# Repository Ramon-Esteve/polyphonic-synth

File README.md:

# DIY Polyphonic Analog Synthesizer

A university project building a polyphonic analog synthesizer from scratch using [mki x es.EDU](https://www.ericasynths.lv/shop/diy-kits-1/mki-x-esedu-diy-system/) module designs and an STM32 Nucleo board as a MIDI-to-CV controller.

The goal is to go from a single voice on a breadboard to a playable multi-voice analog synth controlled via MIDI — while documenting every step of the process.

## What This Project Is

This is an educational build that combines:
- **Analog circuit design** — VCO, VCF, VCA and envelope circuits based on the publicly available Erica Synths / Moritz Klein educational module designs
- **Embedded firmware** — STM32 Nucleo running custom MIDI-to-CV firmware (MIDI parsing, DAC output, voice allocation)
- **System integration** — bridging the digital (MIDI) and analog (CV/gate) worlds to create a playable instrument

All analog circuits are prototyped on breadboard. The Nucleo board handles MIDI input and outputs control voltages (1V/oct pitch CV, gate, and additional CV for filter/PWM) through its DAC and an op-amp scaling stage.

## Current Status

> **Phase 1 — VCO + MIDI pitch control** *(in progress)*

- [x] VCO built and working on breadboard
- [x] VCO on dedicated PCB (`220526_VCO_V2`) — validated and tested under real circuit conditions
- [ ] Nucleo DAC output verified
- [ ] Op-amp CV scaling circuit (0–3.3V → 0–5V)
- [ ] MIDI input (USB or UART @ 31250 baud)
- [ ] MIDI note-to-CV conversion with 1V/oct tracking
- [ ] Gate output
- [ ] Calibration and tuning

## Build Phases

| Phase | Module | Description | Status |
|-------|--------|-------------|--------|
| 1 | VCO + MIDI-to-CV | Pitch control of a single oscillator via MIDI keyboard | In progress |
| 2 | VCA + Envelope | Amplitude control with gate/envelope from Nucleo | Planned |
| 3 | VCF | Voltage-controlled filter with CV control of cutoff | Planned |
| 4 | Polyphony | Duplicate voice chains, multi-channel DAC, voice allocation | Planned |

## Hardware

- **Microcontroller:** STM32 Nucleo board (<!-- replace with your specific model, e.g. Nucleo-F446RE -->)
- **Analog modules:** Based on mki x es.EDU circuit designs (VCO, VCA, VCF, Envelope)
- **Prototyping:** Breadboard (switched from stripboard after killing two ICs soldering — lesson learned)
- **DAC output stage:** Op-amp scaling circuit to convert Nucleo's 0–3.3V DAC to 0–5V+ for 1V/oct

## VCO V2 — Bring-Up & Verification (June 2026)

The first custom VCO PCB revision (`220526_VCO_V2`, JLCPCB) has passed full bring-up and verification.

**Verified:**
- Power integrity: rails at ±11.8/−11.9 V, both wire-bridged traces (−12V rail, R7 network) confirmed functional (0.4 Ω continuity, voltage-verified under load)
- Full signal chain: saw core → buffer → AC coupling → ×3.13 gain stage → SAW out (~10 Vpp), comparator → divider → PULSE out (8.88 Vpp)
- PWM: full duty sweep functional, clean latch behaviour only at threshold extremes (by design)
- Frequency range: **~5 Hz to ~49.8 kHz** (full audio range + LFO territory)
- **V/oct tracking: ~10 cents over 2 octaves** after trimming ADJ_TUNE1, verified via Voxengo SPAN — better than the breadboard baseline (~14 ct/oct). Residual error will be handled by the planned STM32 autotune routine.

**Known issues → fixed in V0.2:**
- D4 LED footprint connects to the CV summing node instead of the buffered SAW output (not populated on V2)
- Two manufacturing trace defects bridged with wire (new revision removes bridges)
- Expo converter (BC548/BC558 discrete pair) to be replaced with monolithic matched pair (BC847BS) + tempco resistor

Full measurement protocol: [`docs/bringup_vco_v2/bringup_checklist_VCO_V2.md`](docs/bringup_vco_v2/bringup_checklist_VCO_V2.md)
Test equipment: Tektronix 2225, TOOLTOP ET828 Pro, PeakTech 6225A, RME Fireface + Voxengo SPAN

| VCO V2 PCB | Square wave output on scope |
|---|---|
|  |  |
## Repository Structure

```
├── docs/                   # Build documentation for each module
├── firmware/               # STM32CubeIDE project — MIDI-to-CV firmware
├── schematics/             # Circuit diagrams and breadboard layouts
├── measurements/           # Tuning data, oscilloscope captures, test results
├── media/                  # Build photos, video material, audio samples
└── references/             # Datasheets, links, related projects
```

## Documentation

Each build phase is documented with:
- Circuit description and design rationale
- Breadboard layout and build notes
- Test procedures and measurements
- Problems encountered and how they were solved

Video documentation accompanies the written docs — see the [media/](media/) folder or the <!-- add link to your YouTube/channel here --> video series.

## Key References

- [mki x es.EDU module manuals](https://www.ericasynths.lv/shop/diy-kits-1/mki-x-esedu-diy-system/) — free PDFs covering circuit design from scratch
- [Moritz Klein's YouTube channel](https://www.youtube.com/@MoritzKlein0) — companion videos to the EDU modules
- [ModSynth MIDI2CV](https://warrantyvoids.github.io/ModSynth/modules/midi2cv/) — STM32 Nucleo-based MIDI-to-CV reference project
- [STM32 DAC getting started](https://wiki.st.com/stm32mcu/wiki/Getting_started_with_DAC) — official ST tutorial

## License

This project is licensed under the MIT License — see [LICENSE](LICENSE) for details.

Note: The analog circuit designs are based on the mki x es.EDU educational series by Erica Synths and Moritz Klein. Their manuals are freely available but the original designs remain their work. This repository contains my own implementation, firmware, documentation, and modifications.

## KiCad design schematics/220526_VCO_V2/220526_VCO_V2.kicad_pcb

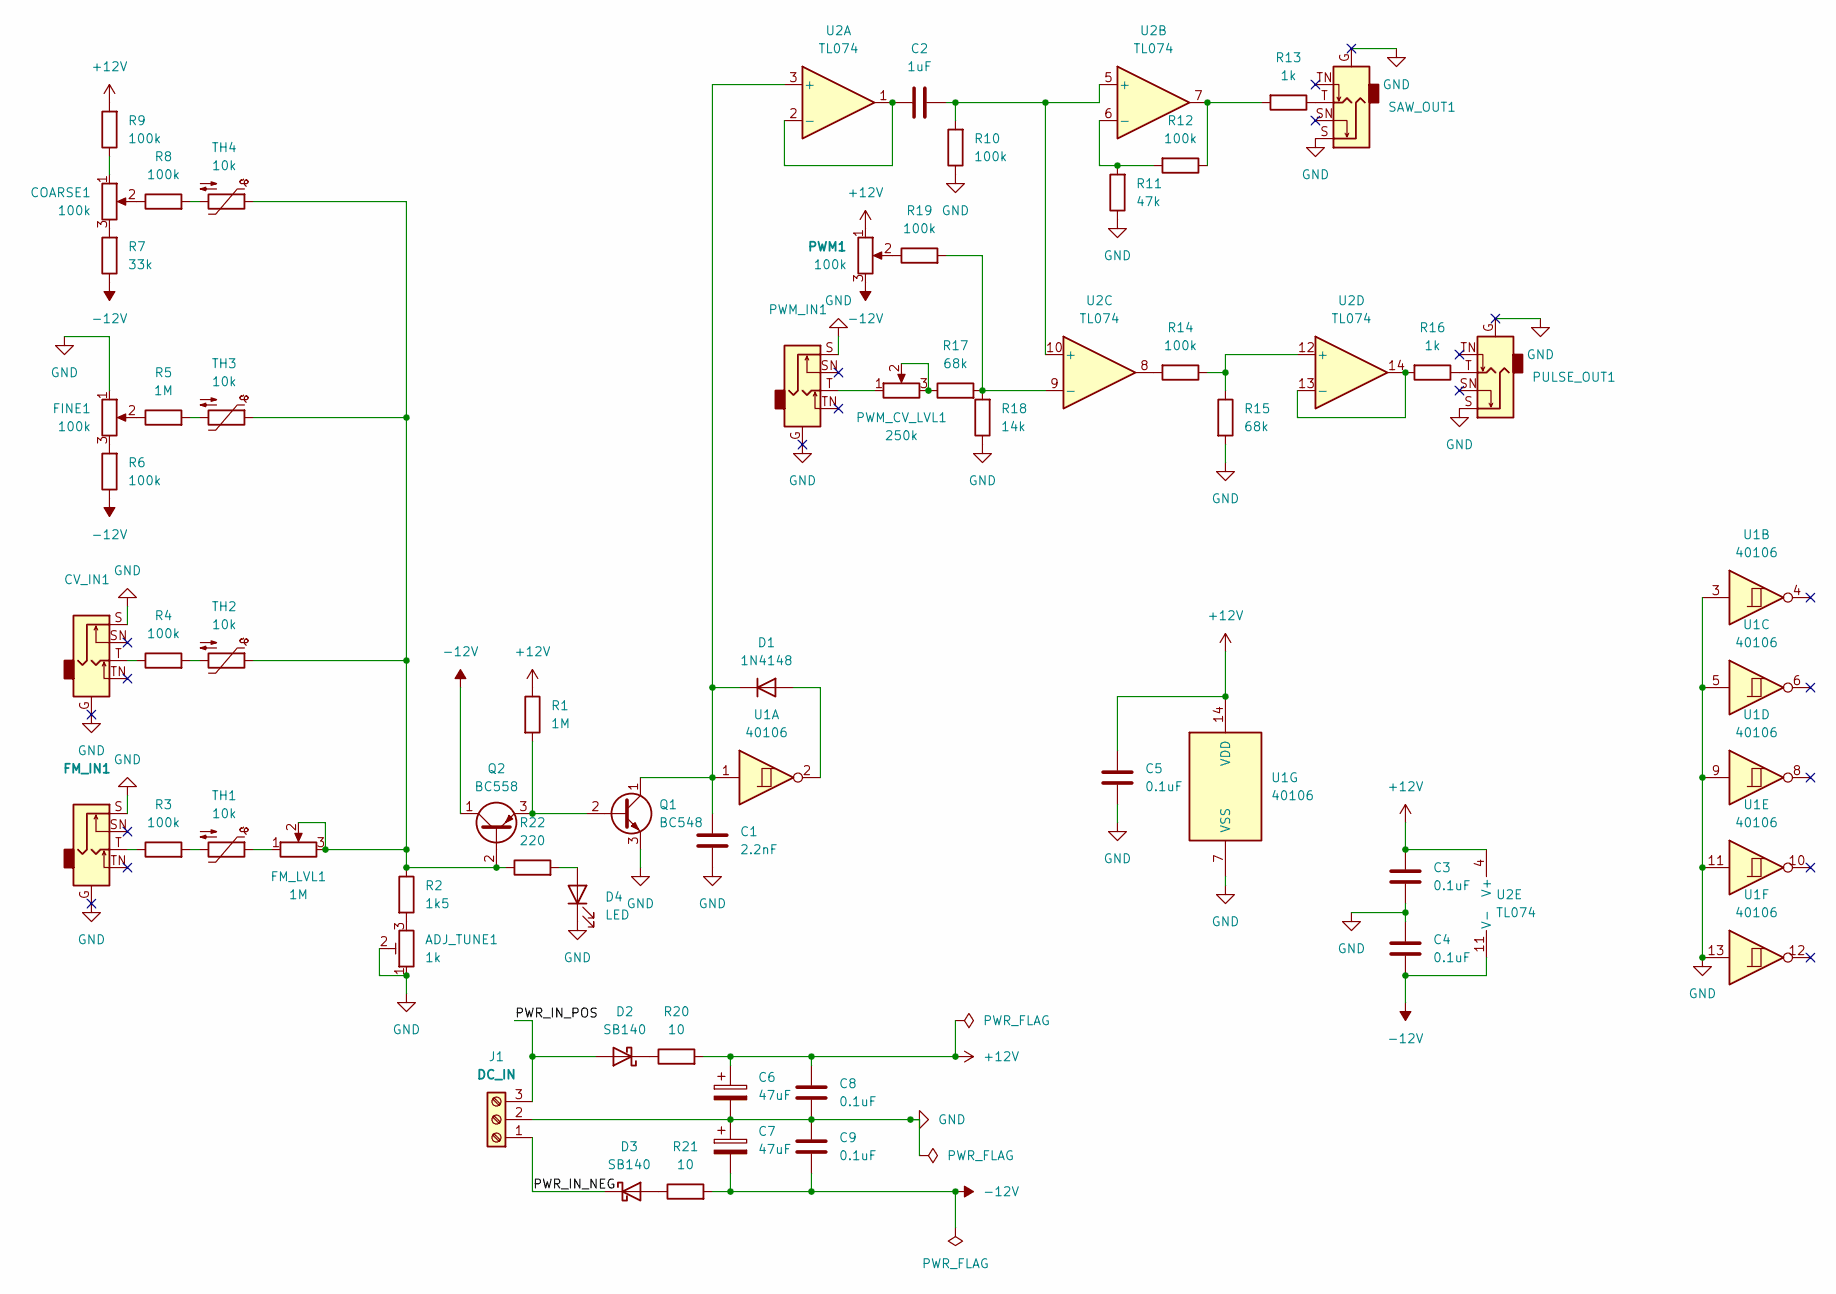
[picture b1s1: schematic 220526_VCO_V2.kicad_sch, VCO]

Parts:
ADJ_TUNE1: 1k; Potentiometer_Bourns_3266W_Vertical
C1: 2.2nF; C_Rect_L13.0mm_W4.0mm_P10.00mm_FKS3_FKP3_MKS4
C2: 1uF; C_Rect_L7.2mm_W5.0mm_P5.00mm
C3, C4, C5, C8, C9: 0.1uF; C_Disc_D5.1mm_W3.2mm_P5.00mm
C6, C7: 47uF; C_Radial_D5.0mm_H11.0mm_P2.00mm
COARSE1: 100k; Potentiometer_Omeg_PC16BU_Vertical
CV_IN1: AudioJack2_Ground_Switch; Jack_3.5mm_Cliff_FCR1281_Horizontal
D1: 1N4148; D_DO-35_SOD27_P7.62mm_Horizontal
D2, D3: SB140; D_DO-41_SOD81_P10.16mm_Horizontal
D4: LED; LED_D5.0mm
FINE1: 100k; Potentiometer_Omeg_PC16BU_Vertical
FM_IN1: AudioJack2_Ground_Switch; Jack_3.5mm_Cliff_FCR1281_Horizontal
FM_LVL1: 1M; Potentiometer_Omeg_PC16BU_Vertical
J1: DC_IN; TerminalBlock_RND_205-00288_1x03_P5.08mm_Horizontal
PULSE_OUT1: AudioJack2_Ground_Switch; Jack_3.5mm_Cliff_FCR1281_Horizontal
PWM1: 100k; Potentiometer_Omeg_PC16BU_Vertical
PWM_CV_LVL1: 250k; Potentiometer_Omeg_PC16BU_Vertical
PWM_IN1: AudioJack2_Ground_Switch; Jack_3.5mm_Cliff_FCR1281_Horizontal
Q1: BC548; TO-92_Inline
Q2: BC558; TO-92_Inline
R1, R5: 1M; R_Axial_DIN0207_L6.3mm_D2.5mm_P10.16mm_Horizontal
R2: 1k5; R_Axial_DIN0207_L6.3mm_D2.5mm_P10.16mm_Horizontal
R3, R4, R6, R8, R9, R10, R12, R14, R19: 100k; R_Axial_DIN0207_L6.3mm_D2.5mm_P10.16mm_Horizontal
R7: 33k; R_Axial_DIN0207_L6.3mm_D2.5mm_P10.16mm_Horizontal
R11: 47k; R_Axial_DIN0207_L6.3mm_D2.5mm_P10.16mm_Horizontal
R13, R16: 1k; R_Axial_DIN0207_L6.3mm_D2.5mm_P10.16mm_Horizontal
R15, R17: 68k; R_Axial_DIN0207_L6.3mm_D2.5mm_P10.16mm_Horizontal
R18: 14k; R_Axial_DIN0207_L6.3mm_D2.5mm_P10.16mm_Horizontal
R20, R21: 10; R_Axial_DIN0207_L6.3mm_D2.5mm_P10.16mm_Horizontal
R22: 220; R_Axial_DIN0207_L6.3mm_D2.5mm_P10.16mm_Horizontal
SAW_OUT1: AudioJack2_Ground_Switch; Jack_3.5mm_Cliff_FCR1281_Horizontal
TH1, TH2, TH3, TH4: 10k; R_Axial_DIN0204_L3.6mm_D1.6mm_P5.08mm_Horizontal
U1: 40106; DIP-14_W7.62mm_Socket
U2: TL074; DIP-14_W7.62mm_Socket

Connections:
+12V: C3.1, C5.1, C6.1, C8.1, PWM1.1, R1.1, R9.2, R20.2, U1.14 (VDD), U2.4 (V+)
-12V: C4.2, C7.2, C9.2, PWM1.3, Q2.1 (C), R6.1, R7.1, R21.2, U2.11 (V-)
/PWR_IN_NEG: D3.1 (K), J1.1
/PWR_IN_POS: D2.2 (A), J1.3
GND: ADJ_TUNE1.1, ADJ_TUNE1.2, C1.2, C3.2, C4.1, C5.2, C6.2, C7.1, C8.2, C9.1, CV_IN1.G, CV_IN1.S, D4.1 (K), FINE1.1, FM_IN1.G, FM_IN1.S, J1.2, PULSE_OUT1.G, PULSE_OUT1.S, PWM_IN1.G, PWM_IN1.S, Q1.3 (E), R10.1, R11.1, R15.2, R18.1, SAW_OUT1.G, SAW_OUT1.S, U1.3, U1.5, U1.7 (VSS), U1.9, U1.11, U1.13
unnamed: ADJ_TUNE1.3, R2.2
unnamed: COARSE1.1, R9.1
unnamed: COARSE1.2, R8.1
unnamed: COARSE1.3, R7.2
unnamed: CV_IN1.T, R4.1
unnamed: D1.2 (A), U1.2
unnamed: C1.1, D1.1 (K), Q1.1 (C), U1.1, U2.3 (+)
unnamed: D2.1 (K), R20.1
unnamed: D3.2 (A), R21.1
unnamed: D4.2 (A), R22.2
unnamed: FINE1.2, R5.1
unnamed: FINE1.3, R6.2
unnamed: FM_IN1.T, R3.1
unnamed: FM_LVL1.1, TH1.1
unnamed: PULSE_OUT1.T, R16.1
unnamed: PWM1.2, R19.1
unnamed: PWM_CV_LVL1.1, PWM_IN1.T
unnamed: PWM_CV_LVL1.2, PWM_CV_LVL1.3, R17.1
unnamed: Q1.2 (B), Q2.3 (E), R1.2
unnamed: FM_LVL1.2, FM_LVL1.3, Q2.2 (B), R2.1, R22.1, TH2.1, TH3.1, TH4.1
unnamed: R3.2, TH1.2
unnamed: R4.2, TH2.2
unnamed: R5.2, TH3.2
unnamed: R8.2, TH4.2
unnamed: R12.1, R13.2, U2.7
unnamed: R13.1, SAW_OUT1.T
unnamed: R14.2, U2.8
unnamed: C2.1, U2.1, U2.2 (-)
unnamed: C2.2, R10.2, U2.5 (+), U2.10 (+)
unnamed: R11.2, R12.2, U2.6 (-)
unnamed: R17.2, R18.2, R19.2, U2.9 (-)
unnamed: R14.1, R15.1, U2.12 (+)
unnamed: R16.2, U2.13 (-), U2.14

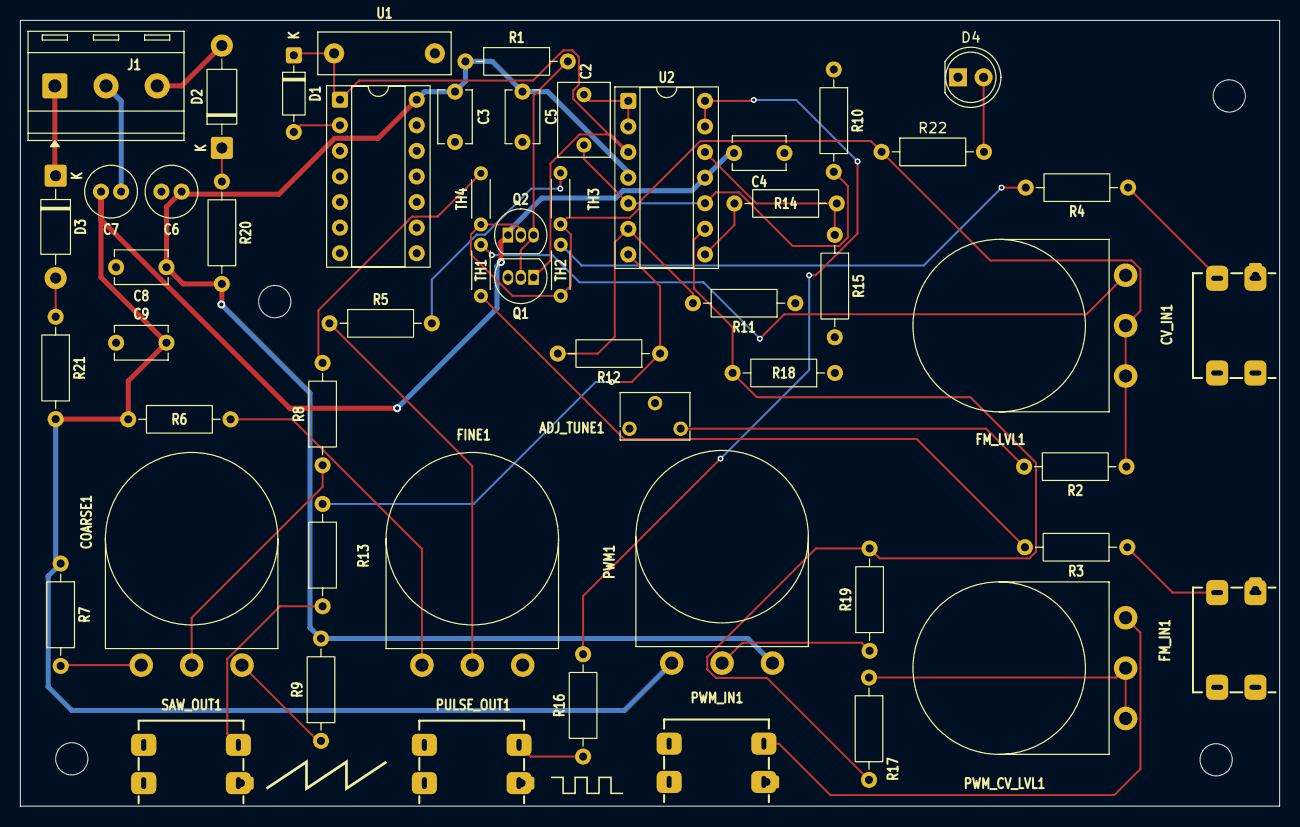
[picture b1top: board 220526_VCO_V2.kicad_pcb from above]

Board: 2 copper layers, 125.0 x 78.0 mm, 55 parts (0 on the bottom side), 38 nets.

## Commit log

2026-02-27 add project folder structure
2026-04-18 add VCO milestone demo and update Phase 1 status
2026-05-27 add VCO schematic and gerbers
2026-05-27 add midi_to_cv
2026-05-27 remove midi_to_cv, starting fresh
2026-05-27 chore: initial repo scaffold
2026-05-27 chore(cubemx): initial project generation for nucleo-f446re
2026-05-27 build tinyusb
2026-06-09 feat(hardware): add poly synth main board KiCad schematic
    Initial commit of 020623_SYNTH KiCad 10 project.
    Top-level schematic for the paraphonic synthesizer —
    VCOs, VCF, VCA, MIDI-CV, power supply sections.
2026-06-09 docs(hardware): VCO V2 bring-up protocol, photos and README update
    - Full measurement checklist: power integrity, DC operating points,
    signal chain verification (Phase 0-4)
    - V/oct tracking trimmed to ~10 ct over 2 octaves (SPAN-verified)
    - Frequency range 5 Hz - 49.8 kHz confirmed
    - Scope photos (Tektronix 2225 + TOOLTOP ET828 Pro) linked inline
    - Known issues for V0.2 revision documented
2026-06-09 docs(hardware): add scope photos to README VCO V2 section
2026-06-09 docs(hardware): fix photo captions in README VCO V2 section
2026-06-09 docs: update current status — VCO on dedicated PCB
